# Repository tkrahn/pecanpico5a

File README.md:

pecanpico5a
===========

The fifth version of the Pecan Pico board and the associated software. Note that the Rx/Tx lines from the micro to the gps are switched. This requires soldering a crossover bridge.

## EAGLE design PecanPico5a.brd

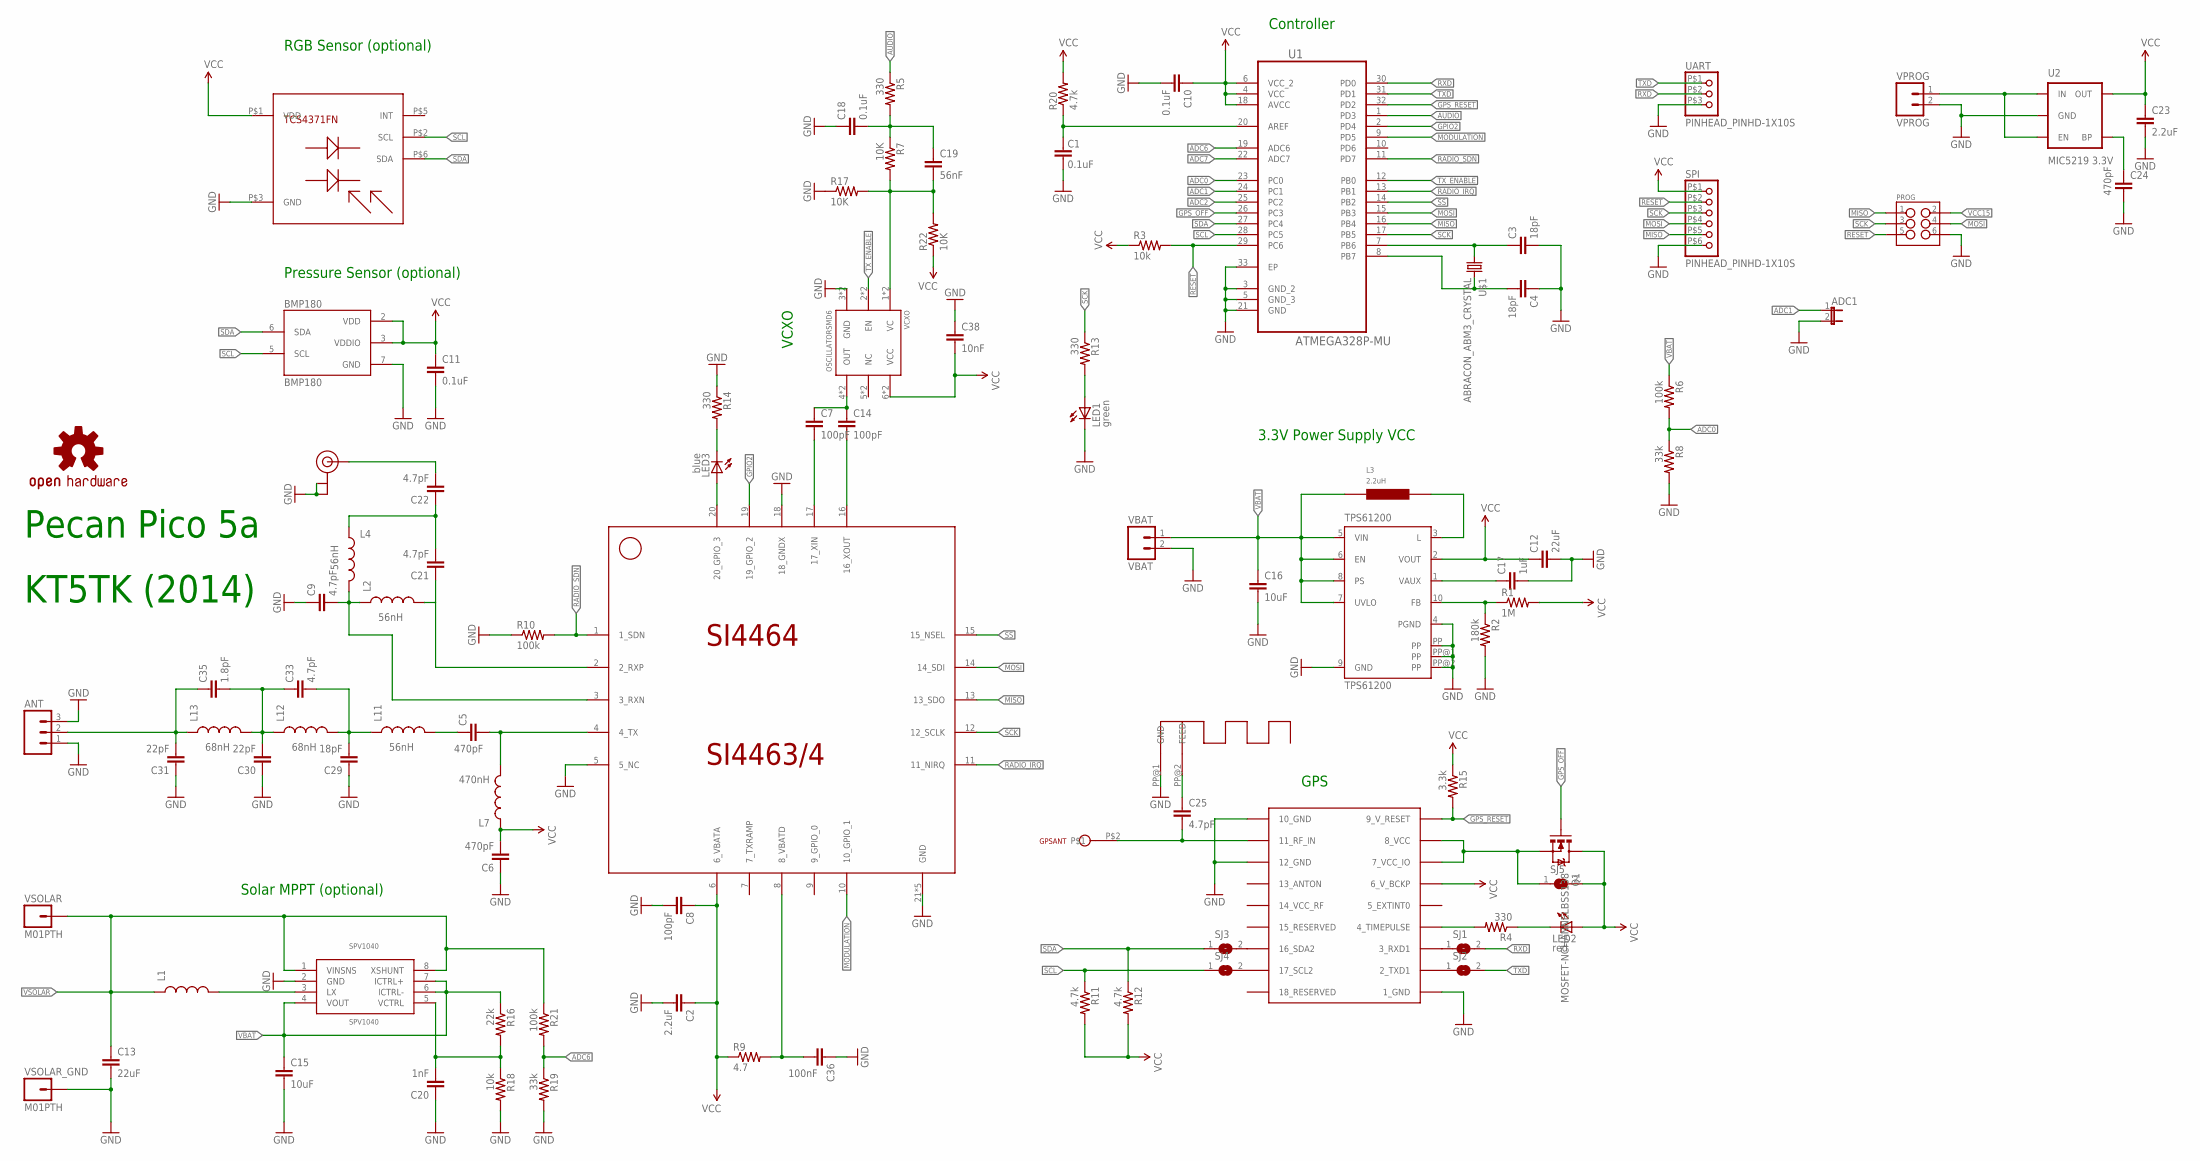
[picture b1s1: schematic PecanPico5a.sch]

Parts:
ADC1: JUMPER-2SMD-NO-NS; SJ_2S-NO-NS
ANT: M03PTH; 1X03
BMP180: BMP180
C1, C10, C11, C18: 0.1uF; 0402-CAP
C2, C23: 2.2uF; 0603-CAP
C3, C4, C29: 18pF; 0402-CAP
C5, C6, C24: 470pF; 0402-CAP
C7, C8, C14: 100pF; 0402-CAP
C9, C21, C22, C25, C33: 4.7pF; 0402-CAP
C12, C13: 22uF; 0805
C15, C16: 10uF; 0805
C17: 1uF; 0805
C19: 56nF; 0402-CAP
C20: 1nF; 0402-CAP
C30, C31: 22pF; 0402-CAP
C35: 1.8pF; 0402-CAP
C36: 100nF; 0402-CAP
C38: 10nF; 0402-CAP
GPSANT: 1X1S; 1_27X1_PINHEAD_1X10S
L1: SPARKFUN_INDUCTOR1007; SPARKFUN_1007
L2, L4, L11: 56nH; 0603
L3: 2.2uH; LPS3015
L7: 470nH; 0603
L12, L13: 68nH; 0603
LED1: green; LED-0603
LED2: red; LED-0603
LED3: blue; LED-0603
LOGO1: OSHW-LOGOS; OSHW-LOGO-S
PROG: M03X22X3_SILK_SM; 2X3
Q1: MOSFET-NCHANNELBSS138; SOT23
R1: 1M; 0402-RES
R2: 180k; 0402-RES
R3, R18: 10k; 0402-RES
R4, R5, R13, R14: 330; 0402-RES
R6, R10, R21: 100k; 0402-RES
R7, R17, R22: 10K; 0402-RES
R8, R19: 33k; 0402-RES
R9: 4.7; 0402-RES
R11, R12, R20: 4.7k; 0402-RES
R15: 3.3k; 0402-RES
R16: 22k; 0402-RES
SI4464: SI4463/4; QFN-20
SJ1, SJ2, SJ3, SJ4, SJ5: SJ
SPI: PINHEAD_PINHD-1X10S; PINHEAD_1X10S
SPV1040: SPV1040; TSSOP8
TCS4371FN: TCS4371FN; TCS3471FN
TPS61200: TPS61200; S-PDSO-N10
U1: ATMEGA328P-MU; QFN50P500X500X100-33N
U2: MIC5219 3.3V; SOT23-5
U$1: ABRACON_ABM3_CRYSTAL
U$2: U.FL
U$3: UBLOX_MAX-6
U$4: GPS_MEANDER; GPS_INV_F_MEANDER
UART: PINHEAD_PINHD-1X10S; PINHEAD_1X10S
VBAT: VBAT; 1X02
VCXO: OSCILLATORSMD6; CRYSTAL-SMD-7.5X5.2-6PIN
VPROG: VPROG; 1X02
VSOLAR: M01PTH; 1X01
VSOLAR_GND: M01PTH; 1X01

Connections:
ADC0: R6.2, R8.1, U1.23 (PC0)
ADC1: ADC1.1, U1.24 (PC1)
ADC2: U1.25 (PC2)
ADC6: R19.1, R21.2, U1.19 (ADC6)
ADC7: U1.22 (ADC7)
AREF: C1.2, R20.1, U1.20 (AREF)
AUDIO: R5.1, U1.1 (PD3)
GND: ADC1.2, ANT.1, ANT.3, BMP180.7 (GND), C1.1, C2.2, C3.2, C4.1, C6.1, C8.2, C9.1, C10.2, C11.2, C12.2, C13.2, C15.2, C16.2, C17.2, C18.1, C20.1, C23.2, C24.2, C29.1, C30.1, C31.1, C36.1, C38.1, LED1.C, PROG.6, R2.2, R8.2, R10.1, R14.1, R17.1, R18.2, R19.2, SI4464.5 (5_NC), SI4464.18 (18_GNDX), SI4464.21 (GND), SI4464.22 (GND), SI4464.23 (GND), SI4464.24 (GND), SI4464.25 (GND), SPI.P$6 (6), SPV1040.2 (GND), TCS4371FN.P$3 (GND), TPS61200.4 (PGND), TPS61200.9 (GND), TPS61200.PP, TPS61200.PP@1 (PP), TPS61200.PP@2 (PP), U1.3 (GND_2), U1.5 (GND_3), U1.21 (GND), U1.33 (EP), U2.2 (GND), U$2.P$1 (GND), U$2.P$2 (GND), U$3.1_GND, U$3.10_GND, U$3.12_GND, U$4.PP@1 (GND), UART.P$3 (3), VBAT.2, VCXO.3 (GND), VCXO.3INNER (GND), VPROG.2, VSOLAR_GND.1
GPIO2: SI4464.19 (19_GPIO_2), U1.2 (PD4)
GPS_OFF: Q1.1 (G), U1.26 (PC3)
GPS_RESET: R15.2, U1.32 (PD2), U$3.9_V_RESET
MISO: PROG.1, SI4464.13 (13_SDO), SPI.P$5 (5), U1.16 (PB4)
MOD1: C18.2, C19.1, R5.2, R7.1
MODULATION: SI4464.10 (10_GPIO_1), U1.9 (PD5)
MOSI: PROG.4, SI4464.14 (14_SDI), SPI.P$4 (4), U1.15 (PB3)
unnamed: C14.2, SI4464.16 (16_XOUT)
unnamed: C25.2, GPSANT.P$2, U$3.11_RF_IN
unnamed: L3.P$2 (2), TPS61200.3 (L)
unnamed: R1.1, R2.1, TPS61200.10 (FB)
unnamed: LED2.C, R4.1
unnamed: C17.1, TPS61200.1 (VAUX)
unnamed: R4.2, U$3.4_TIMEPULSE
unnamed: C3.1, U1.7 (PB6), U$1.P$1 (1)
unnamed: C4.2, U1.8 (PB7), U$1.P$2 (2)
unnamed: C7.1, C14.1, VCXO.4 (OUT), VCXO.4INNER (OUT)
unnamed: SJ1.1, U$3.3_RXD1
unnamed: SJ2.1, U$3.2_TXD1
unnamed: C19.2, R7.2, R17.2, R22.2, VCXO.1 (VC), VCXO.1INNER (VC)
unnamed: LED1.A, R13.2
unnamed: C5.2, L7.2, SI4464.4 (4_TX)
unnamed: C21.1, L2.2, SI4464.2 (2_RXP)
unnamed: SJ3.2, U$3.16_SDA2
unnamed: SJ4.2, U$3.17_SCL2
unnamed: C5.1, L11.2
unnamed: C30.2, C33.1, C35.2, L12.1, L13.2
unnamed: LED3.A, SI4464.20 (20_GPIO_3)
unnamed: LED3.C, R14.2
unnamed: C7.2, SI4464.17 (17_XIN)
unnamed: L1.2, SPV1040.3 (LX)
unnamed: C9.2, L2.1, L4.2, SI4464.3 (3_RXN)
unnamed: C29.2, C33.2, L11.1, L12.2
unnamed: ANT.2, C31.2, C35.1, L13.1
unnamed: C20.2, R16.2, R18.1, SPV1040.5 (VCTRL)
unnamed: C21.2, C22.1, L4.1
unnamed: Q1.2 (S), SJ5.1, U$3.7_VCC_IO, U$3.8_VCC
unnamed: C22.2, U$2.P$3 (SIGNAL)
unnamed: U2.1 (IN), U2.3 (EN), VPROG.1
unnamed: C36.2, R9.2, SI4464.8 (8_VBATD)
unnamed: C24.1, U2.4 (BP)
unnamed: C25.1, U$4.PP@2 (FEED)
RADIO_IRQ: SI4464.11 (11_NIRQ), U1.13 (PB1)
RADIO_SDN: R10.2, SI4464.1 (1_SDN), U1.11 (PD7)
RESET: PROG.5, R3.2, SPI.P$2 (2), U1.29 (PC6)
RXD: SJ1.2, U1.30 (PD0), UART.P$2 (2)
SCK: PROG.3, R13.1, SI4464.12 (12_SCLK), SPI.P$3 (3), U1.17 (PB5)
SCL: BMP180.5 (SCL), R11.1, SJ4.1, TCS4371FN.P$2 (SCL), U1.28 (PC5)
SDA: BMP180.6 (SDA), R12.1, SJ3.1, TCS4371FN.P$6 (SDA), U1.27 (PC4)
SS: SI4464.15 (15_NSEL), U1.14 (PB2)
TXD: SJ2.2, U1.31 (PD1), UART.P$1 (1)
TX_ENABLE: U1.12 (PB0), VCXO.2 (EN), VCXO.2INNER (EN)
VBAT: C15.1, C16.1, L3.P$1 (1), R6.1, R16.1, SPV1040.4 (VOUT), SPV1040.6 (ICTRL-), SPV1040.7 (ICTRL+), TPS61200.5 (VIN), TPS61200.6 (EN), TPS61200.7 (UVLO), TPS61200.8 (PS), VBAT.1
VCC15: BMP180.2 (VDD), BMP180.3 (VDDIO), C2.1, C6.2, C8.1, C10.1, C11.1, C12.1, C23.1, C38.2, L7.1, LED2.A, PROG.2, Q1.3 (D), R1.2, R3.1, R9.1, R11.2, R12.2, R15.1, R20.2, R22.1, SI4464.6 (6_VBATA), SJ5.2, SPI.P$1 (1), TCS4371FN.P$1 (VDD), TPS61200.2 (VOUT), U1.4 (VCC), U1.6 (VCC_2), U1.18 (AVCC), U2.5 (OUT), U$3.6_V_BCKP, VCXO.6 (VCC), VCXO.6INNER (VCC)
VSOLAR: C13.1, L1.1, R21.1, SPV1040.1 (VINSNS), SPV1040.8 (XSHUNT), VSOLAR.1

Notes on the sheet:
KT5TK (2014)
Controller
3.3V Power Supply VCC
GPS
VCXO
Pressure Sensor (optional)
RGB Sensor (optional)
Pecan Pico 5a
Solar MPPT (optional)

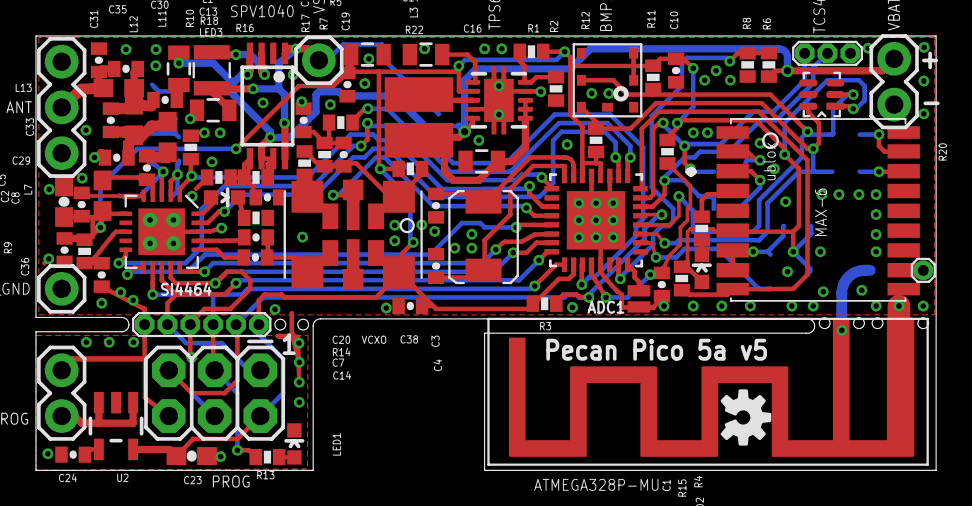
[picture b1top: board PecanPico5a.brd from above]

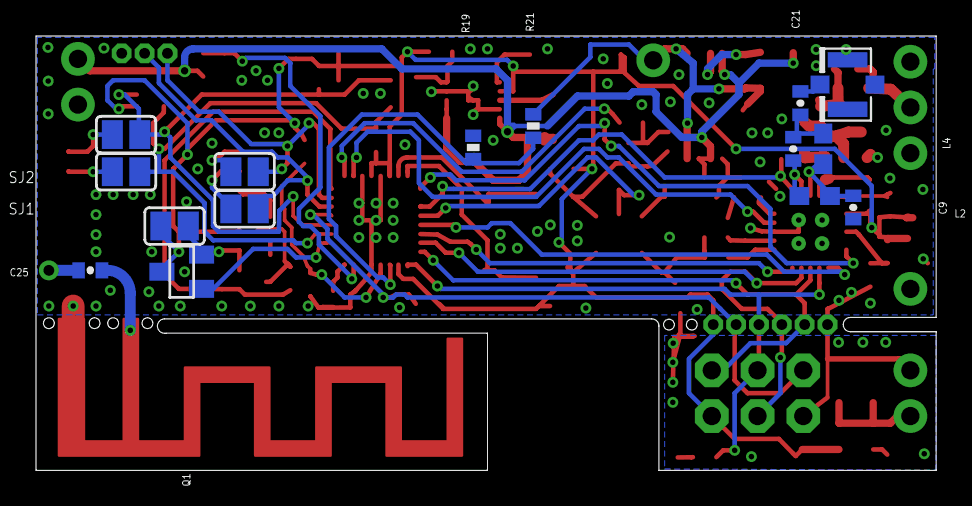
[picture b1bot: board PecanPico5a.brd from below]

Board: 2 copper layers, 50.0 x 24.1 mm, 94 parts (15 on the bottom side), 61 nets.

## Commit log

2014-10-24 Added Eagle files & Gerbers
2015-04-16 Update radio_si446x.cpp
    According to AN633 (https://www.silabs.com/Support%20Documents/TechnicalDocs/AN633.pdf, p.15 chapter 7.2.1.) the CTS state is reported vie SPI in the 8 SCLK cycles after issuing READ_CMD_BUFF (0x44).
    The value returned in parallel while issuing READ_CMD_BUFF is (at least in my case) not a valid CTS state. As the code interpreted the value returned in parallel as the CTS state, the reply loop, wai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
    Fixed by inserting another SPI.transfer just before. Now each loop takes 16 SCLK cycles.

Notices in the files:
parts and their libraries:
SparkFun-FreqCtrl_TK: Licensing: CC v3.0 Share-Alike You are welcome to use this library for commercial purposes.
